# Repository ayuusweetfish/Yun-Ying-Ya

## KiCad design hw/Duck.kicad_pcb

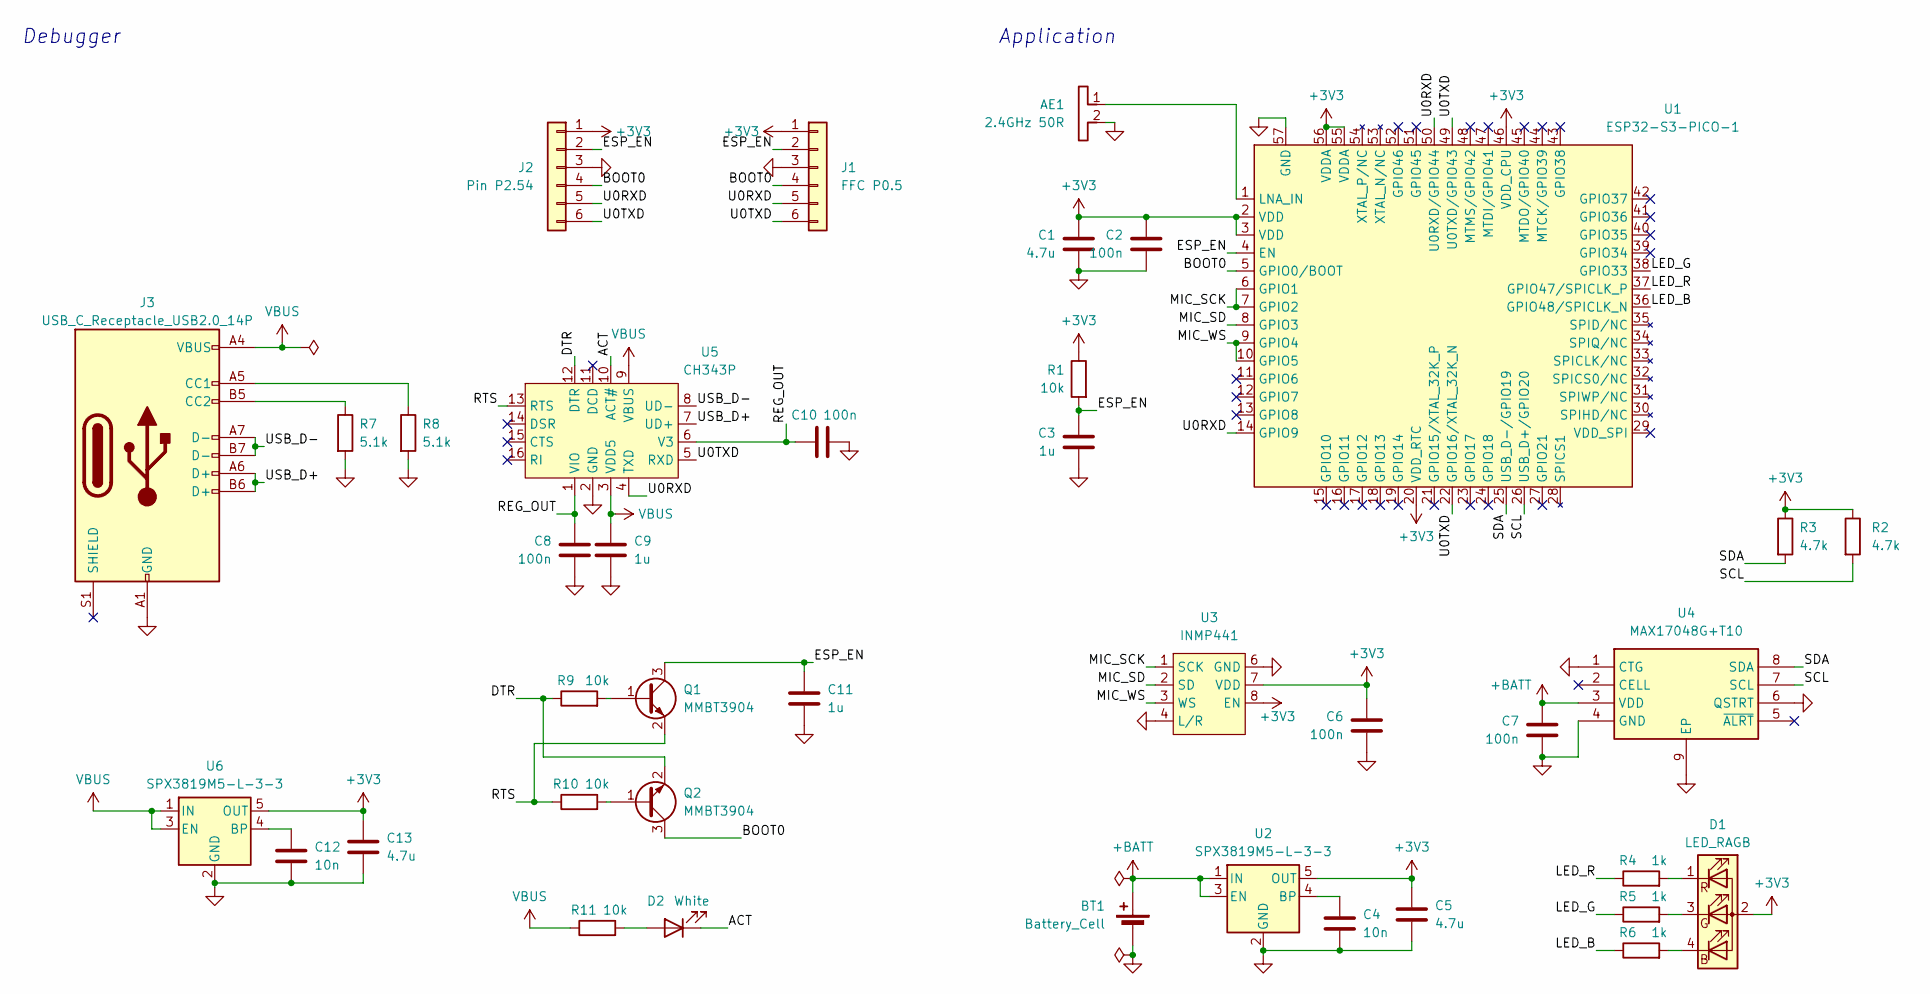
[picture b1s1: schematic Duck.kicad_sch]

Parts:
AE1: 2.4GHz 50R; ANT_IFA_USB_2.4GHz_50R
BT1: Battery_Cell; JST_GH_SM02B-GHS-TB_1x02-1MP_P1.25mm_Horizontal
C1, C5, C13: 4.7u; C_0402_1005Metric
C2, C6, C7, C8, C10: 100n; C_0402_1005Metric
C3, C9, C11: 1u; C_0402_1005Metric
C4, C12: 10n; C_0402_1005Metric
D1: LED_RAGB; LED_1x04_D5.0_P1.27
D2: White; LED_0603_1608Metric
J1: FFC P0.5; TestPoints_FFC_1x06_P0.5
J2: Pin P2.54; PinHeader_1x06_P2.54mm_Vertical
J3: USB_C_Receptacle_USB2.0_14P; USB_C_Receptacle
Q1, Q2: MMBT3904; SOT-23
R1, R9, R10, R11: 10k; R_0402_1005Metric
R2, R3: 4.7k; R_0402_1005Metric
R4, R5, R6: 1k; R_0402_1005Metric
R7, R8: 5.1k; R_0402_1005Metric
U1: ESP32-S3-PICO-1; ESP32-S3-PICO-1-LGA-56
U2, U6: SPX3819M5-L-3-3; SOT-23-5
U3: INMP441
U4: MAX17048G+T10; SON50P200X200X80-9N-D; Manufacturer_Part_Number MAX17048G+T10; Mouser Part Number 700-MAX17048G+T10
U5: CH343P; QFN-16-1EP_3x3mm_P0.5mm_EP1.9x1.9mm

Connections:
+3V3: C1.1, C2.1, C5.1, C6.1, C13.1, D1.2 (A), J1.1, J2.1, R1.1, R2.1, R3.1, U1.2 (VDD), U1.3 (VDD), U1.20 (VDD_RTC), U1.46 (VDD_CPU), U1.55 (VDDA), U1.56 (VDDA), U2.5 (OUT), U3.7 (VDD), U3.8 (EN), U6.5 (OUT)
+BATT: BT1.1 (+), C7.1, U2.1 (IN), U2.3 (EN), U4.3 (VDD)
/ACT: D2.1 (K), U5.10 (ACT#)
/BOOT0: J1.4, J2.4, Q2.3 (C), U1.5 (GPIO0/BOOT)
/DTR: Q2.2 (E), R9.1, U5.12 (DTR)
/ESP_EN: C3.1, C11.1, J1.2, J2.2, Q1.3 (C), R1.2, U1.4 (EN)
/LED_B: R6.1, U1.36 (GPIO48/SPICLK_N)
/LED_G: R5.1, U1.38 (GPIO33)
/LED_R: R4.1, U1.37 (GPIO47/SPICLK_P)
/MIC_SCK: U1.6 (GPIO1), U1.7 (GPIO2), U3.1 (SCK)
/MIC_SD: U1.8 (GPIO3), U3.2 (SD)
/MIC_WS: U1.9 (GPIO4), U1.10 (GPIO5), U3.3 (WS)
/REG_OUT: C8.1, C10.1, U5.1 (VIO), U5.6 (V3)
/RTS: Q1.2 (E), R10.1, U5.13 (RTS)
/SCL: R2.2, U1.26 (USB_D+/GPIO20), U4.7 (SCL)
/SDA: R3.2, U1.25 (USB_D-/GPIO19), U4.8 (SDA)
/U0RXD: J1.5, J2.5, U1.14 (GPIO9), U1.50 (U0RXD/GPIO44), U5.4 (TXD)
/U0TXD: J1.6, J2.6, U1.22 (GPIO16/XTAL_32K_N), U1.49 (U0TXD/GPIO43), U5.5 (RXD)
/USB_D+: J3.A6 (D+), J3.B6 (D+), U5.7 (UD+)
/USB_D-: J3.A7 (D-), J3.B7 (D-), U5.8 (UD-)
GND: AE1.2, BT1.2 (-), C1.2, C2.2, C3.2, C4.2, C5.2, C6.2, C7.2, C8.2, C9.2, C10.2, C11.2, C12.2, C13.2, J1.3, J2.3, J3.A1 (GND), J3.A12 (GND), J3.B1 (GND), J3.B12 (GND), R7.2, R8.2, U1.57 (GND), U2.2 (GND), U3.4 (L/R), U3.5 (GND), U3.6 (GND), U3.9 (GND), U4.1 (CTG), U4.4 (GND), U4.6 (QSTRT), U4.9 (EP), U5.2 (GND), U5.17 (GND), U6.2 (GND)
unnamed: D1.4 (BK), R6.2
unnamed: D1.3 (GK), R5.2
unnamed: D1.1 (RK), R4.2
unnamed: D2.2 (A), R11.2
unnamed: J3.A5 (CC1), R8.1
unnamed: J3.B5 (CC2), R7.1
unnamed: Q1.1 (B), R9.2
unnamed: Q2.1 (B), R10.2
unnamed: AE1.1, U1.1 (LNA_IN)
unnamed: C4.1, U2.4 (BP)
unnamed: C12.1, U6.4 (BP)
VBUS: C9.1, J3.A4 (VBUS), J3.A9 (VBUS), J3.B4 (VBUS), J3.B9 (VBUS), R11.1, U5.3 (VDD5), U5.9 (VBUS), U6.1 (IN), U6.3 (EN)

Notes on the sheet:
Debugger
Application

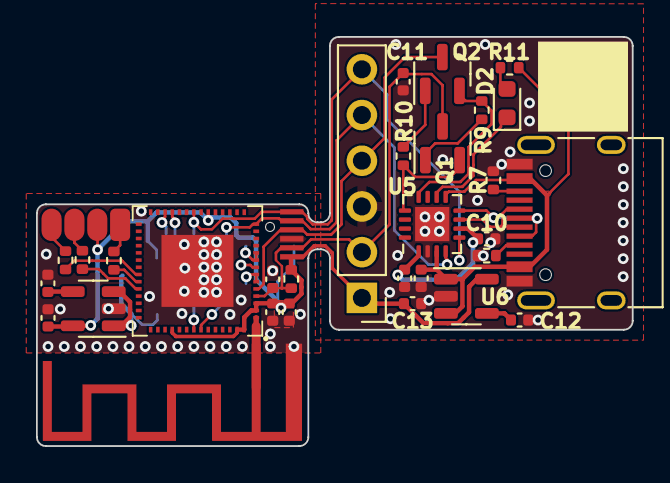
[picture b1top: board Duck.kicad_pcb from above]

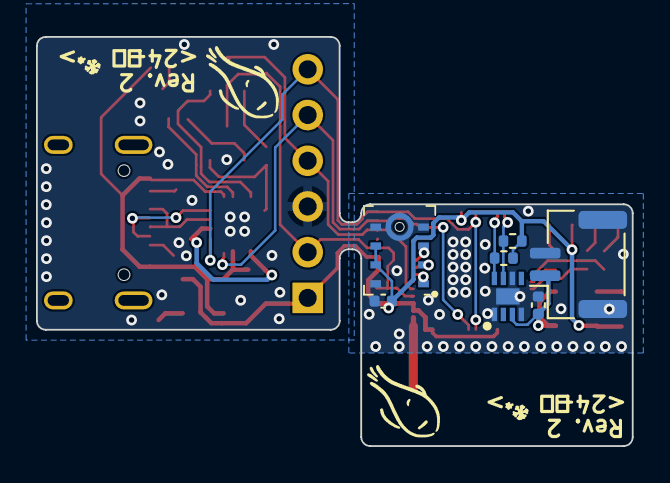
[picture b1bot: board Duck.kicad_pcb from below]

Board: 2 copper layers, 33.1 x 22.7 mm, 39 parts (7 on the bottom side), 33 nets.

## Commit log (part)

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2024-11-10 🎉 Add check & visualisation tool
2024-11-12 Test LLM integration (iFlytek)
2024-11-12 Hello world firmware
2024-11-17 Support more output formats (Lua functions, JavaScript functions)
2024-11-18 server: Switch to 01.AI
2024-11-18 server: Programmatically interface with LLM!
2024-11-19 server: Adjust prompts
2024-11-19 server: Minor adjustments
2024-11-19 fw: HTTP requests
2024-11-19 fw: Put Wi-Fi and HTTP in dedicated compilation units
2024-11-19 fw: Sync time with NTP server
2024-11-19 fw: HTTPS
2024-11-19 fw: Simplify HTTP client event handling
2024-11-19 fw: 🚧 Enterprise Wi-Fi
2024-11-19 fw: 🚧 Enterprise Wi-Fi...??
2024-11-20 fw: Enable PSRAM
2024-11-20 fw: I2S read
2024-11-20 fw: Enable pull down on I2S data pin
2024-11-21 Revert "fw: 🚧 Enterprise Wi-Fi (probably skipping)"
    This reverts commit 0745472ca29eb167ad7444771342a1c00f29d3e9.
2024-11-21 fw: Add ESP-SR
2024-11-21 fw: Correctly enable AFE with noise suppression
    Barring "Ringbuffer of AFE is full." warnings
2024-11-21 fw: Reading I2S in audio loop
2024-11-21 fw: Wake-up words 🎉
2024-11-21 fw: Switch to a TTS-trained model ("Hi, Miaomiao")
2024-11-24 misc: Add C-based cryptographic implementations
2024-11-24 misc: Correctly signing payload according to srun portal
2024-11-24 misc: 🚧 Complete login request
2024-11-24 misc: Complete working login URL
2024-11-24 misc: Sequence requests
2024-11-24 misc: Refactor network authentication into reusable library
2024-11-24 fw: Connect to open Wi-Fi with HTTP-based auth 🚧
2024-11-24 fw: Connected to Internet through Tsinghua SSID 🎉
2024-11-24 server: Integrate Google's API
2024-11-24 server: Tweak prompts
2024-11-25 fw: Clean-ups
2024-11-25 server: Speech recognition endpoint authentication (iFlytek)
2024-11-25 server: Expose a working speech recognition endpoint
2024-11-25 fw: Save speech into a buffer
2024-11-26 server: Switch test to chunked encoding
2024-11-26 hw: Initial schematic and libraries
2024-11-26 hw: Finish schematic
2024-11-26 hw: Avoid IO26 due to module internal routing
2024-11-26 hw: Layout
2024-11-26 hw: Minor revisions
2024-11-27 hw: Finalize (...or is it?)
2024-11-27 hw: Finalize; submit for fab (Rev. 1)
2024-11-27 hw: Adjust silkscreen text position (resubmit)
2024-11-28 fw: Clean up HTTP request subroutines
2024-11-28 fw, server: Upload speech to server for recognition
    TODO: Receive response; Nginx configuration for chunked requests
2024-11-28 fw: Stream write; receive response
2024-11-28 server: Add test endpoint for dumping audio to file
2024-11-28 fw: Misc. clean-ups
2024-11-29 fw: Testing with onboard LED
    ESP32-S3-DevKitC-1 v1.0, LED = GPIO48
2024-11-30 server: Receive gzipped payload
2024-12-01 misc: Move updated Lua visualisation to LOVE
2024-12-02 misc: Add Opus encode test program
2024-12-02 fw: Add audio codec component (unused)
2024-12-02 fw: Pull microphone enable pin high
2024-12-03 fw: Add power management (no effect?)
2024-12-04 server: Refactor to incorporate different LLMs 🚧
2024-12-04 server: Adjust prompts; bring back two-step setup
2024-12-05 server: Complete pipeline from speech to commands 🎉
2024-12-05 server: Unify environment variable names
2024-12-05 server: Unify testruns
2024-12-05 server: Avoid empty lines in response
2024-12-05 server: Add `flicker()` function for the LLM to use
2024-12-05 server: Monitor Lua timeout
2024-12-06 fw: Monitor CPU usage
2024-12-06 fw: Implement LED state transitions
2024-12-07 server: Log all interactions and network activity
2024-12-07 fw: Add sleep test
2024-12-07 server: Fully implement response 🎉
2024-12-07 server: Document how to extract recordings
2024-12-09 fw: Correctly enter modem- & light-sleep
2024-12-09 fw: Restore to previously running program
2024-12-09 hw: Create ECAD models for ESP32-S3-PICO-1
2024-12-09 hw: 🚧 Revision
2024-12-09 hw: 🚧 Adjustments; layout?
2024-12-10 fw: Keep LEDC PWM running during light sleep
2024-12-10 fw: Enable ULP 💡💤
2024-12-10 fw: 小鸭小鸭 🦆🎉
2024-12-10 hw: Further simplify 🚧
2024-12-10 hw: Most of the polish
2024-12-10 hw: Hopefully all finished; polish in the details to-do
2024-12-11 hw: Finalize PCB details
2024-12-11 hw: Schematic page layout
2024-12-11 hw: Revise schematic and update PCB; resubmit (Rev. 2)
2024-12-11 hw: Fix missing power line (/_<); resubmit (Rev. 2)
2024-12-14 fw: 🚧 Go to sleep and fix race conditions in LED update task
2024-12-14 fw: 🚧 Capture ULP wake-ups
2024-12-14 fw: Change to shared-memory flags to avoid wake-up signal misses
2024-12-14 fw: Move to semaphores, finally 🎉💤
2024-12-15 fw: Set LED GPIO output strength
2024-12-16 fw: 🚧 Test ULP speed limits
2024-12-16 fw: Optimised ULP GPIO read
2024-12-16 fw: Inspect `RTC_FAST_CLK` frequency
2024-12-16 fw: Confirmed ULP correctly clocked by XTAL/2 🎉
2024-12-16 fw: Clean up
2024-12-16 fw: Measure instruction cycles
2024-12-19 fw: Run on board Rev. 2
2024-12-20 fw: Explicitly specify required components within ESP-IDF
2024-12-20 fw: Upgrade ESP-IDF to v5.3.2
2024-12-20 fw: (Mostly) correctly output I2S clock signals from LEDC
2024-12-20 fw: 🚧 Read more bits in ULP?
2024-12-20 fw: Read 20 bits in ULP!
2024-12-20 fw: 24 bits at ULP
2024-12-21 fw: Revert semaphores in LED routine
    ... which increases current consumption (6.05 mA -> 9.15 mA). Needs further investigation
2024-12-21 fw: Thresholding and hysteresis for gating
2024-12-22 fw: Resolve LED task suspension/power consumption issue
2024-12-23 fw: Ease audio stream inspection
2024-12-23 fw: Work around bit timing issue after reset?
2024-12-24 fw: Switch between ULP and I2S peripheral
2024-12-24 fw: Pump audio data to AFE again
2024-12-25 server, fw: Optimise/refactor light animations
2024-12-25 fw: Reduce latency before rainbow glow
2024-12-25 fw: Monitor background noise in ULP
2024-12-25 fw: Detect end-of-speech by threshold
2024-12-25 fw: Resolve race condition in audio pause/resume
2024-12-25 server: 🚧 Resolving WebSocket closed-by-remote issue
2024-12-25 server, fw: Correctly handle remote early-close scenario; resolve truncated audio
2024-12-25 fw: Upgrade dependencies
    Specifically, upgrade ESP-SR to 1.9.5 where 小鸭小鸭 model is bundled
2024-12-26 fw: Robust battery fuel gauge handling
    Barring a reset on disconnection
2024-12-26 fw: Slightly optimise current consumption
2024-12-26 fw: 🚧 Feed external (non-I2S) data into audio input stream
2024-12-26 fw: Send audio data from ULP to main CPU
2024-12-26 fw: Feed ULP-collected data to ESP-SR frontend
2024-12-26 fw: Switch to ESP-SR's VAD for more accurate speech activity detection
2024-12-28 fw: Increase startup signal light intensity
2024-12-30 fw: Fix previous refactor, working now
2024-12-30 fw: 🚧 Directly push ULP-captured samples?
2024-12-30 fw: 🚧 Dump ULP-captured waveform
2024-12-30 fw: Increase console baud rate to 921600
2024-12-30 fw: Bring back the main loop (🚧 Almost!)
    Only works the first time
2024-12-30 fw: Correctly running main loop 🎉
2024-12-30 fw: 🚧 Adjust thresholds?
2024-12-30 fw: Dump both ULP and I2S streams for comparison
2024-12-30 fw: 🚧 Who knows how this glitches??
2024-12-31 fw: Further attempts to fix glitching audio
2024-12-31 fw: 🚧 Trying to synchronise the timers
2024-12-31 fw: More precise indeed!
2024-12-31 fw: 🚧 But anyway happy Gregorian new year from UTC+8!
2025-01-01 fw: 🚧 Remove unused registers into the assembly block
    ... but is this really possible with ULP-RISC-V?
2025-01-01 fw: Is this better now??
2025-01-01 fw: Revert to aligned edges??
2025-01-02 fw: 🚧🌀
2025-01-02 fw: 🚧 Test ULP cycles
2025-01-02 fw: 🚧 Correctly reading from testbed waveform
2025-01-02 fw: More robust bus readings
2025-01-02 fw: 🚧 NOP sled
2025-01-02 fw: 🚧 More sled
2025-01-02 fw: 🚧 Cycle-accurate compensated!
2025-01-02 fw: Correctly sampling 8~9 bits
2025-01-02 fw: Correctly sample 9 bits
2025-01-03 fw: 🎉 Finally, reading clean signals from ULP
2025-01-03 fw: 🎉 Minor optimisations. Low-power VAD works!
2025-01-03 fw: Reduce unnecessary memory bandwidth
2025-01-04 server: Switch to Lua implementation of sanity checks
2025-01-04 misc: Lua visualiser for the updated format
2025-01-04 misc: Usability improvements in the visualiser
2025-01-04 server, misc: Revise prompt and switch models (DeepSeek v3 & Gemini 2.0 Flash)
2025-01-08 misc: Check maximum packet size after Opus encoding
2025-01-08 fw: Run complete loop, again
2025-01-08 fw: Further improve ULP audio monitoring
    (1) Fill samples' unread LSb's by sign-extending (rounding to zero)
    (2) Add hard-reset in thresholding
2025-01-08 fw: Fixed time interval for the main update loop
2025-01-08 chore: Add proper `.gitignore` and `.gitattributes`
    Also, commit previously moved visualisation programs
2025-01-09 fw: Check connectivity by pinging 1.1.1.1
2025-01-09 fw: Prepare to upgrade ESP-IDF
2025-01-09 fw: 🚧 Opus encoding (WIP)
2025-01-09 fw: Send Opus-encoded packets
2025-01-09 fw: Fix erroneous buffer transmission
2025-01-10 misc: 🚧 Opus decoding from WASM
2025-01-10 misc: WebAssembly Opus decoding 🎉
2025-01-10 server: Decode Opus streams
2025-01-11 fw: Enlarge HTTP response buffer
2025-01-11 server: Fix missing `await` in auto-retry
2025-01-11 server: Save raw request payload instead of decoded PCM
2025-01-12 server: Extend debugging server to Opus-encoded audio
2025-01-13 fw: Attempts at improving effects of the light
2025-12-12 fw: Upgrade project to ESP-IDF v5.5.1 ❄
2025-12-12 fw: Fix link error due to RTC memory usage
    Similar issue: espressif/esp-idf#7073
2025-12-15 fw: Document command to check ULP symbol offset
2025-12-15 fw: Resolve sample rate off by 0.16% issue
2025-12-16 fw: Updates for testing
    1. Lower VAD threshold from 1000 to 600
    2. Correctly run application loop without Wi-Fi configuration (set to no-op)
    Known issue: encode task does not refresh watchdog?
2025-12-17 fw: Adjust window sizes
    - ULP VAD: 64 -> 128 samples (4 -> 8 ms)
    - ESP-SR VAD trigger-clear threshold: 1 -> 1.5 s
    - Seems wake-up word detection triggers less reliably when this is too low (may trigger at next ULP VAD wake-up)
2025-12-18 fw: Clean up I2S clock-related subroutines
2025-12-20 fw: Use convenient macro to specify full/compressed instructions
2025-12-23 fw: Reduce SPI flash size to 4 MiB
    ... for more board compatibility. In particular, this runs on -FH4R2 models
2025-12-23 fw: (WIP) Trying to understand the timers (again?)...
2025-12-23 fw: Reformat edited portions
2025-12-23 fw: Maybe slightly more reliable clock sync (see comments)
2025-12-26 fw: Format delay sled assembly
2025-12-26 fw: Eliminate overcomplicating phase/duty adjustment
2025-12-27 misc: Update Opus encode test program, with libopus build instructions
2025-12-27 server: Make testrun path-compatible with main application
2025-12-27 fw: Fix encoder task taking up all CPU time
    Allows the idle task to run.
    Should ditch `vTaskSuspend()` and rely on semaphores. Should check whether this correctly triggers auto light-sleep.
2025-12-27 fw: Replace unreliable delay with semaphore signaling
2025-12-27 server: Migrate to Aliyun Gummy ASR (WIP)
2025-12-27 server: Finish service migration
2025-12-27 server: Add Qwen to the language model options
2025-12-28 fw: Avoid WPA3 configuration for broader compatibility?
2025-12-28 server: Migrate from Google's Gemini to Qwen-Coder
    Because Google AI Studio radically cut the quota for the free tier (20 RPD).
    Also, fix a regexp overlook for exactly-suffix triple backticks.
2025-12-29 server: Move to Fengari for Lua in JS
    wasmoon strangely causes internal inconsistency in Deno; investigation in progress
2025-12-29 server: Suppress backtrace in Lua error messages
2025-12-29 server: Bind database object to statement rather than `globalThis`
2025-12-30 server: Adapt prompt to Qwen3-Plus
2025-12-30 server: More prompt tuning; move to Qwen3-Coder-Flash for faster responses
2025-12-30 server: Fine-tune parameters; move to Qwen3-Flash for faster responses
2026-01-05 fw: Allow test server IP together with Wi-Fi configuration
2026-01-09 server: Paste speech recognition service documentation link in code
2026-01-18 fw: Upgrade project to ESP-IDF v5.5.2 ❄
